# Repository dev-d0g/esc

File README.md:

4 layer STM32-based trapezoidal ESC with high/low-side PWM control

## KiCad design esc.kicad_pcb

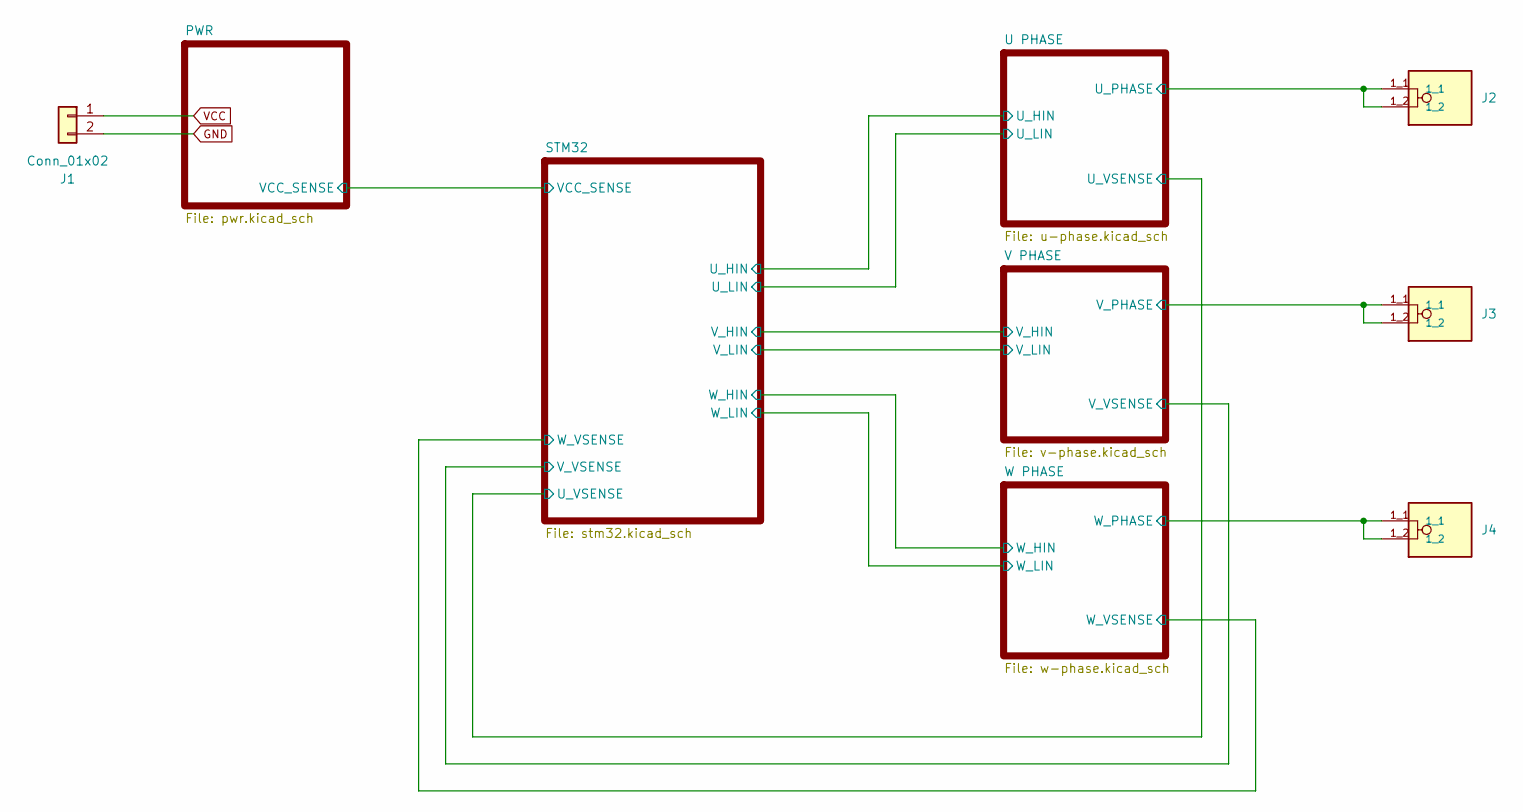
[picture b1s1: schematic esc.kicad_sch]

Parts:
J1: Conn_01x02; JWT_A3963_1x02_P3.96mm_Vertical
J2, J3, J4: Screw_Terminal_01x01; PHOENIX_1706701; PARTREV 24.09.2015

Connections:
/U PHASE/U_PHASE: J2.1_1, J2.1_2; also elsewhere on the board
/V PHASE/V_PHASE: J3.1_1, J3.1_2; also elsewhere on the board
/W PHASE/W_PHASE: J4.1_1, J4.1_2; also elsewhere on the board
GND: J1.2; also elsewhere on the board
VCC: J1.1; also elsewhere on the board

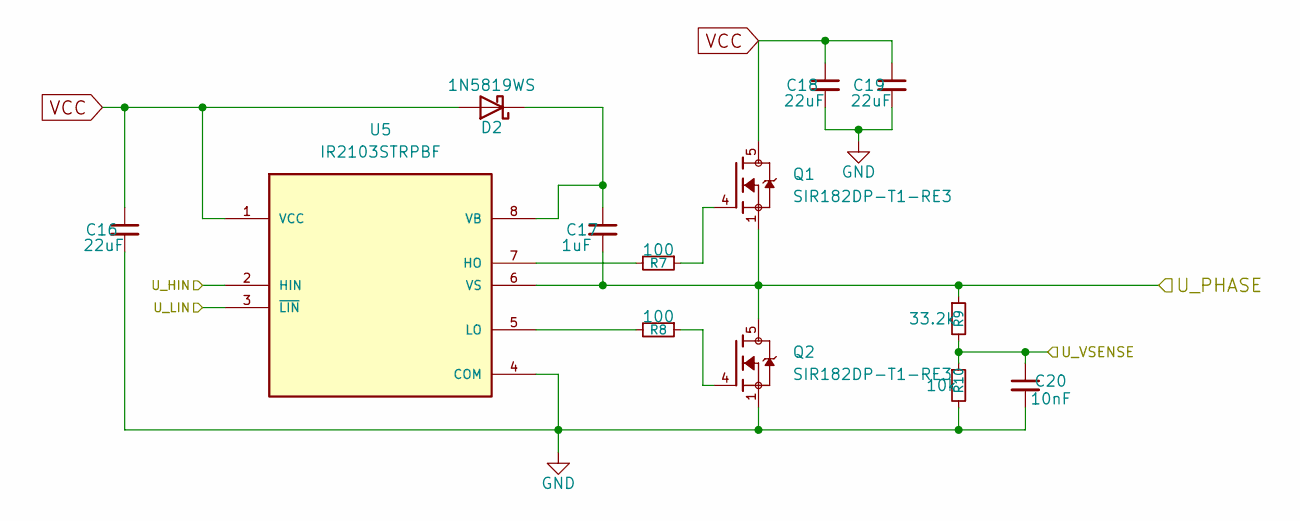
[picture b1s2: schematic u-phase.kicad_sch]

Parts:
C16, C18, C19: 22uF; C_1206_3216Metric
C17: 1uF; C_0805_2012Metric
C20: 10nF; C_0603_1608Metric
D2: 1N5819WS; D_SOD-323
Q1, Q2: SIR182DP-T1-RE3; TRANS_SIR182DP-T1-RE3; PARTREV B
R7, R8: 100; R_1206_3216Metric
R9: 33.2k; R_0805_2012Metric
R10: 10k; R_0805_2012Metric
U5: IR2103STRPBF; SOIC127P600X175-8N; PARTREV April 18, 2013

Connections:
/STM32/U_HIN: U5.2 (HIN); also elsewhere on the board
/STM32/U_LIN: U5.3 (~LIN); also elsewhere on the board
/STM32/U_VSENSE: C20.1, R9.2, R10.1; also elsewhere on the board
/U PHASE/U_PHASE: C17.2, Q1.1, Q1.2, Q1.3, Q2.5, Q2.6, Q2.7, Q2.8, Q2.9, R9.1, U5.6 (VS); also elsewhere on the board
GND: C16.2, C18.2, C19.2, C20.2, Q2.1, Q2.2, Q2.3, R10.2, U5.4 (COM); also elsewhere on the board
unnamed: C17.1, D2.1 (K), U5.8 (VB)
unnamed: Q1.4, R7.1
unnamed: Q2.4, R8.1
unnamed: R7.2, U5.7 (HO)
unnamed: R8.2, U5.5 (LO)
VCC: C16.1, C18.1, C19.1, D2.2 (A), Q1.5, Q1.6, Q1.7, Q1.8, Q1.9, U5.1 (VCC); also elsewhere on the board

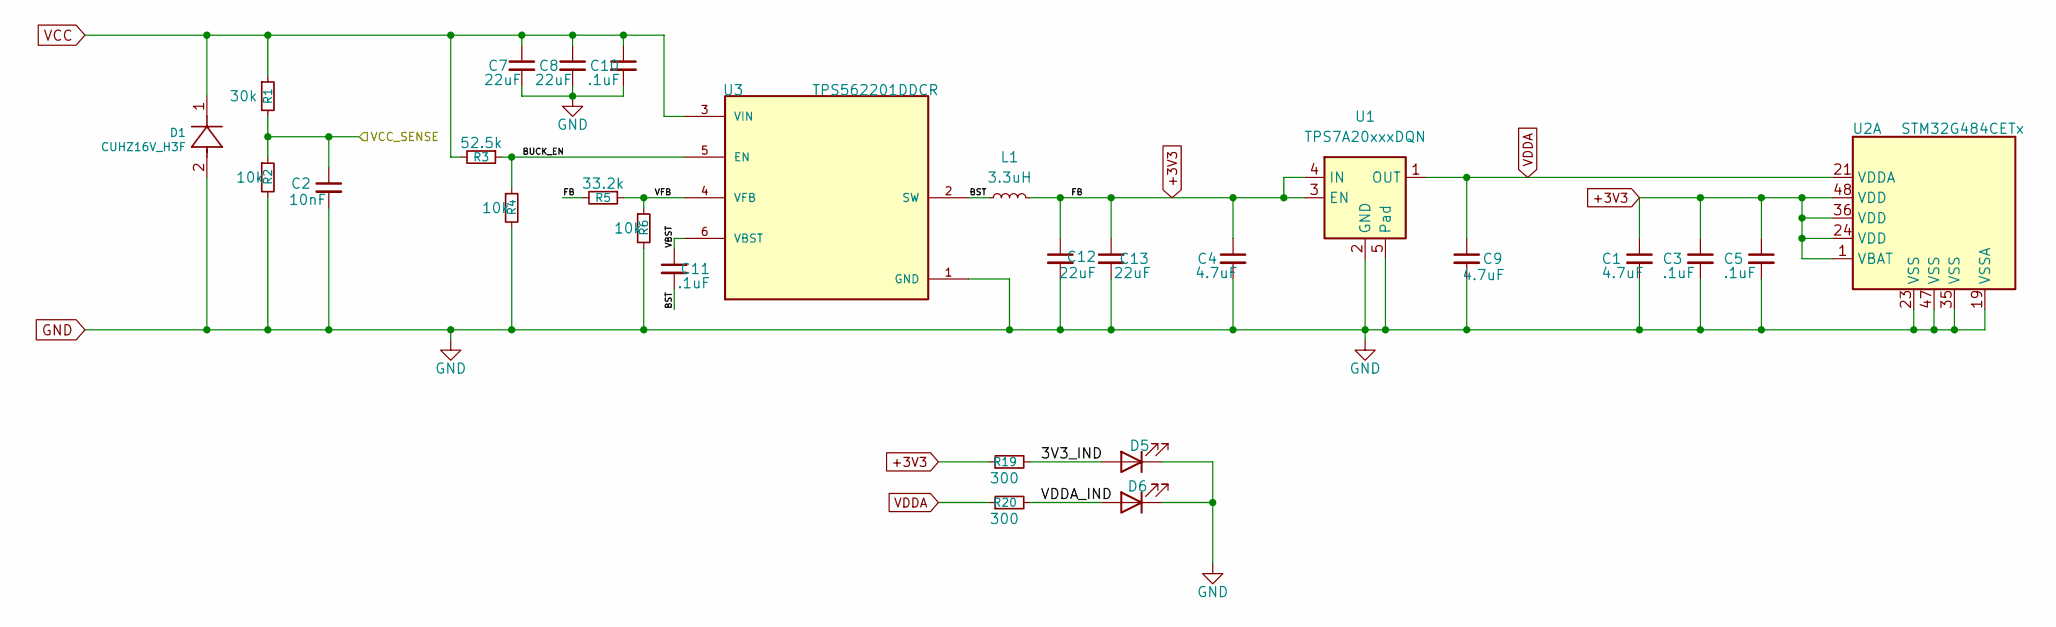
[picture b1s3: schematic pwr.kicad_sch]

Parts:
C1, C4, C9: 4.7uF; C_0805_2012Metric
C2: 10nF; C_0603_1608Metric
C3, C5, C10, C11: .1uF; C_0805_2012Metric
C7, C8, C12, C13: 22uF; C_1206_3216Metric
D1: CUHZ16V_H3F; SOD-323HEUS2H_TOS
D5, D6: LED; LED_0805_2012Metric
L1: 3.3uH; INDC2012X145N
R1: 30k; R_0805_2012Metric
R2, R4, R6: 10k; R_0805_2012Metric
R3: 52.5k; R_0805_2012Metric
R5: 33.2k; R_0805_2012Metric
R19, R20: 300; R_0805_2012Metric
U1: TPS7A20xxxDQN; Texas_X2SON-4_1x1mm_P0.65mm
U2: STM32G484CETx; LQFP-48_7x7mm_P0.5mm
U3: TPS562201DDCR; SOT95P280X110-6N; PARTREV A

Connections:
+3V3: C1.1, C3.1, C4.1, C5.1, C12.1, C13.1, L1.2, R5.2, R19.1, U1.3 (EN), U1.4 (IN), U2.1 (VBAT), U2.24 (VDD), U2.36 (VDD), U2.48 (VDD); also elsewhere on the board
/PWR/3V3_IND: D5.2 (A), R19.2
/PWR/BST: C11.2, L1.1, U3.2 (SW)
/PWR/BUCK_EN: R3.1, R4.1, U3.5 (EN)
/PWR/VBST: C11.1, U3.6 (VBST)
/PWR/VCC_SENSE: C2.1, R1.2, R2.1; also elsewhere on the board
/PWR/VDDA_IND: D6.2 (A), R20.2
/PWR/VFB: R5.1, R6.1, U3.4 (VFB)
GND: C1.2, C2.2, C3.2, C4.2, C5.2, C7.2, C8.2, C9.2, C10.2, C12.2, C13.2, D1.2, D5.1 (K), D6.1 (K), R2.2, R4.2, R6.2, U1.2 (GND), U1.5 (Pad), U2.19 (VSSA), U2.23 (VSS), U2.35 (VSS), U2.47 (VSS), U3.1 (GND); also elsewhere on the board
VCC: C7.1, C8.1, C10.1, D1.1, R1.1, R3.2, U3.3 (VIN); also elsewhere on the board
VDDA: C9.1, R20.1, U1.1 (OUT), U2.21 (VDDA); also elsewhere on the board

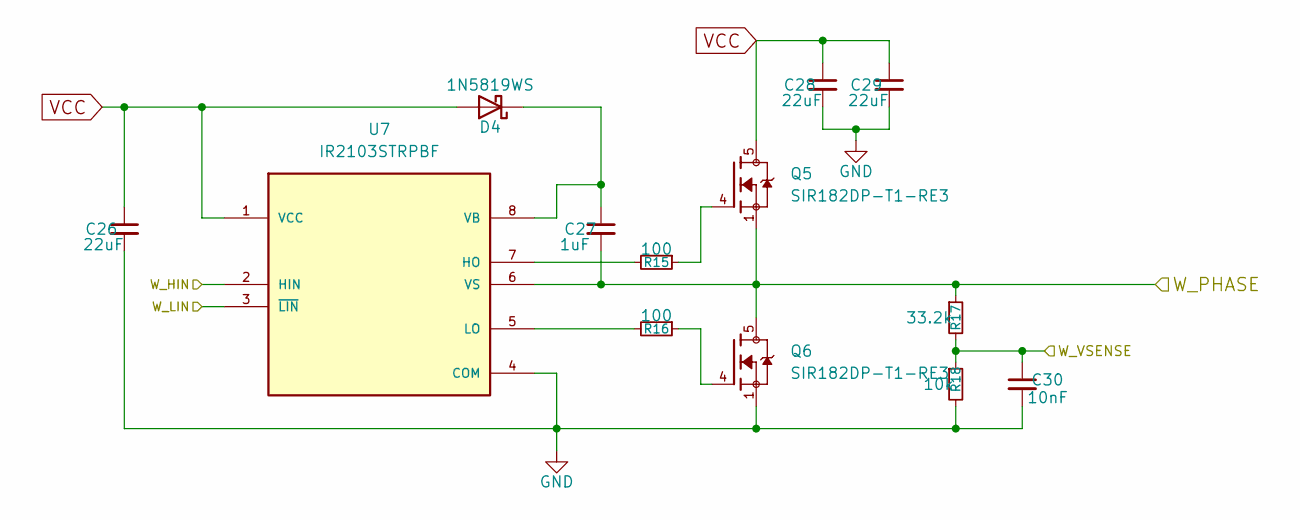
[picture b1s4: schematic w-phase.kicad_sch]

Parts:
C26, C28, C29: 22uF; C_1206_3216Metric
C27: 1uF; C_0805_2012Metric
C30: 10nF; C_0603_1608Metric
D4: 1N5819WS; D_SOD-323
Q5, Q6: SIR182DP-T1-RE3; TRANS_SIR182DP-T1-RE3; PARTREV B
R15, R16: 100; R_1206_3216Metric
R17: 33.2k; R_0805_2012Metric
R18: 10k; R_0805_2012Metric
U7: IR2103STRPBF; SOIC127P600X175-8N; PARTREV April 18, 2013

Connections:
/STM32/W_HIN: U7.2 (HIN); also elsewhere on the board
/STM32/W_LIN: U7.3 (~LIN); also elsewhere on the board
/STM32/W_VSENSE: C30.1, R17.2, R18.1; also elsewhere on the board
/W PHASE/W_PHASE: C27.2, Q5.1, Q5.2, Q5.3, Q6.5, Q6.6, Q6.7, Q6.8, Q6.9, R17.1, U7.6 (VS); also elsewhere on the board
GND: C26.2, C28.2, C29.2, C30.2, Q6.1, Q6.2, Q6.3, R18.2, U7.4 (COM); also elsewhere on the board
unnamed: C27.1, D4.1 (K), U7.8 (VB)
unnamed: Q5.4, R15.1
unnamed: Q6.4, R16.1
unnamed: R15.2, U7.7 (HO)
unnamed: R16.2, U7.5 (LO)
VCC: C26.1, C28.1, C29.1, D4.2 (A), Q5.5, Q5.6, Q5.7, Q5.8, Q5.9, U7.1 (VCC); also elsewhere on the board

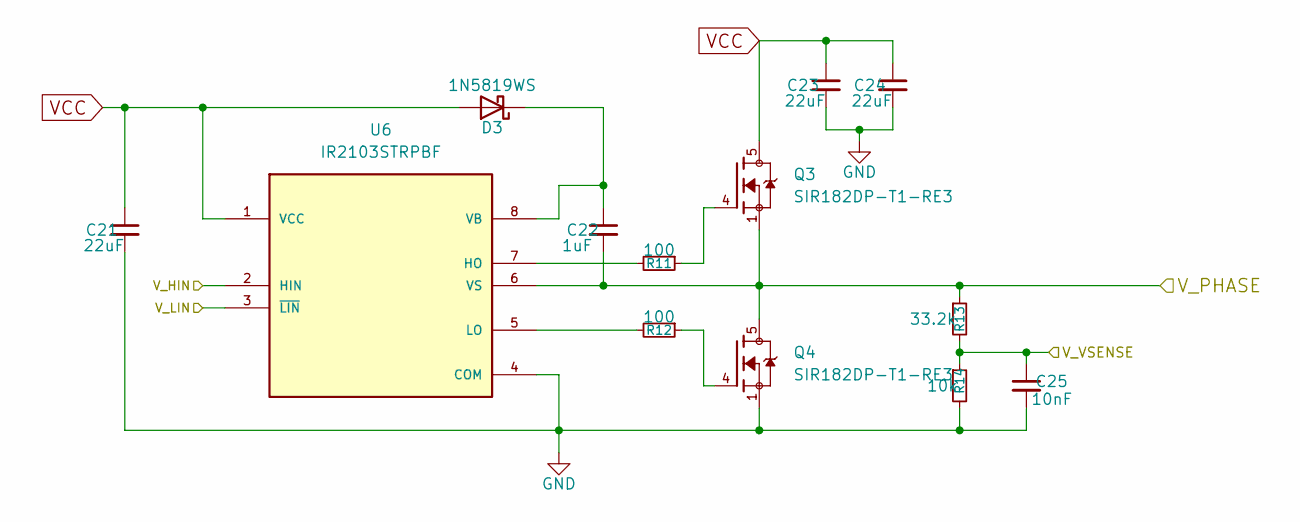
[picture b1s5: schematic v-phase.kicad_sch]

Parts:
C21, C23, C24: 22uF; C_1206_3216Metric
C22: 1uF; C_0805_2012Metric
C25: 10nF; C_0603_1608Metric
D3: 1N5819WS; D_SOD-323
Q3, Q4: SIR182DP-T1-RE3; TRANS_SIR182DP-T1-RE3; PARTREV B
R11, R12: 100; R_1206_3216Metric
R13: 33.2k; R_0805_2012Metric
R14: 10k; R_0805_2012Metric
U6: IR2103STRPBF; SOIC127P600X175-8N; PARTREV April 18, 2013

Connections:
/STM32/V_HIN: U6.2 (HIN); also elsewhere on the board
/STM32/V_LIN: U6.3 (~LIN); also elsewhere on the board
/STM32/V_VSENSE: C25.1, R13.2, R14.1; also elsewhere on the board
/V PHASE/V_PHASE: C22.2, Q3.1, Q3.2, Q3.3, Q4.5, Q4.6, Q4.7, Q4.8, Q4.9, R13.1, U6.6 (VS); also elsewhere on the board
GND: C21.2, C23.2, C24.2, C25.2, Q4.1, Q4.2, Q4.3, R14.2, U6.4 (COM); also elsewhere on the board
unnamed: C22.1, D3.1 (K), U6.8 (VB)
unnamed: Q3.4, R11.1
unnamed: Q4.4, R12.1
unnamed: R11.2, U6.7 (HO)
unnamed: R12.2, U6.5 (LO)
VCC: C21.1, C23.1, C24.1, D3.2 (A), Q3.5, Q3.6, Q3.7, Q3.8, Q3.9, U6.1 (VCC); also elsewhere on the board

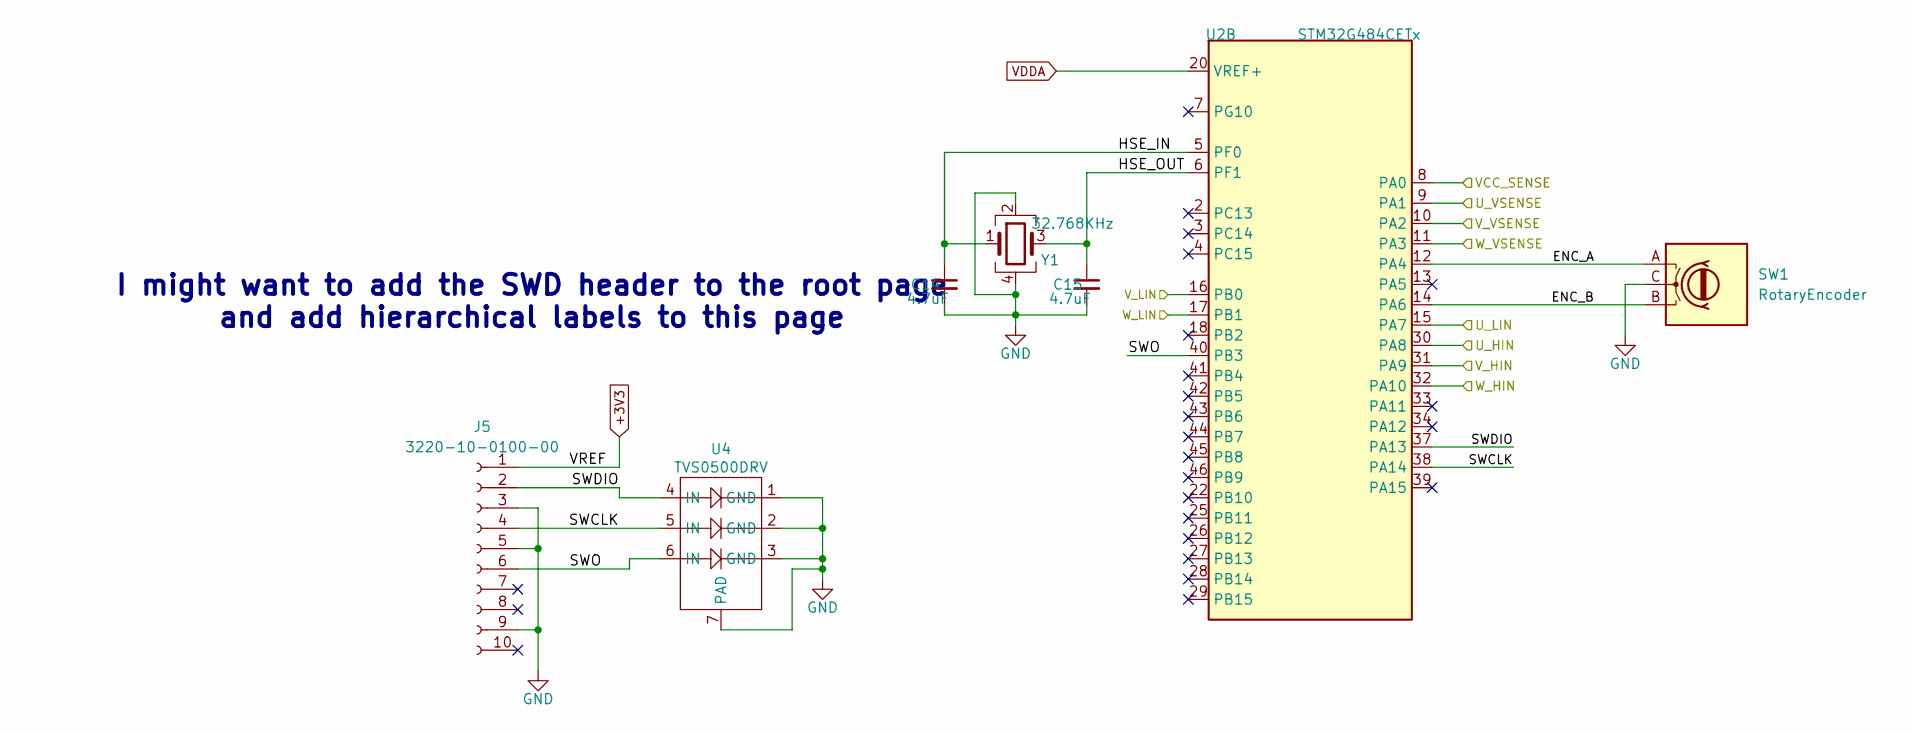
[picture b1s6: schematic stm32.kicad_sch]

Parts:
C14, C15: 4.7uF; C_0805_2012Metric
J5: 3220-10-0100-00; CONN_3220-10-0100-00_CNC
SW1: RotaryEncoder; RotaryEncoder_Alps_EC11E-Switch_Vertical_H20mm
U2: STM32G484CETx; LQFP-48_7x7mm_P0.5mm
U4: TVS0500DRV; SON65P200X200X80-7N
Y1: 32.768KHz; XTAL_ABS04W-32.768KHZ-4-D2-T5; PARTREV 12.18.2018

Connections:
+3V3: J5.1; also elsewhere on the board
/PWR/VCC_SENSE: U2.8 (PA0); also elsewhere on the board
/STM32/ENC_A: SW1.A, U2.12 (PA4)
/STM32/ENC_B: SW1.B, U2.14 (PA6)
/STM32/HSE_IN: C14.1, U2.5 (PF0), Y1.1
/STM32/HSE_OUT: C15.1, U2.6 (PF1), Y1.3
/STM32/SWCLK: J5.4, U2.38 (PA14), U4.5 (IN)
/STM32/SWDIO: J5.2, U2.37 (PA13), U4.4 (IN)
/STM32/SWO: J5.6, U2.40 (PB3), U4.6 (IN)
/STM32/U_HIN: U2.30 (PA8); also elsewhere on the board
/STM32/U_LIN: U2.15 (PA7); also elsewhere on the board
/STM32/U_VSENSE: U2.9 (PA1); also elsewhere on the board
/STM32/V_HIN: U2.31 (PA9); also elsewhere on the board
/STM32/V_LIN: U2.16 (PB0); also elsewhere on the board
/STM32/V_VSENSE: U2.10 (PA2); also elsewhere on the board
/STM32/W_HIN: U2.32 (PA10); also elsewhere on the board
/STM32/W_LIN: U2.17 (PB1); also elsewhere on the board
/STM32/W_VSENSE: U2.11 (PA3); also elsewhere on the board
GND: C14.2, C15.2, J5.3, J5.5, J5.9, SW1.C, U4.1 (GND), U4.2 (GND), U4.3 (GND), U4.7 (PAD), Y1.2, Y1.4; also elsewhere on the board
VDDA: U2.20 (VREF+); also elsewhere on the board

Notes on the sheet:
I might want to add the SWD header to the root page and add hierarchical labels to this page

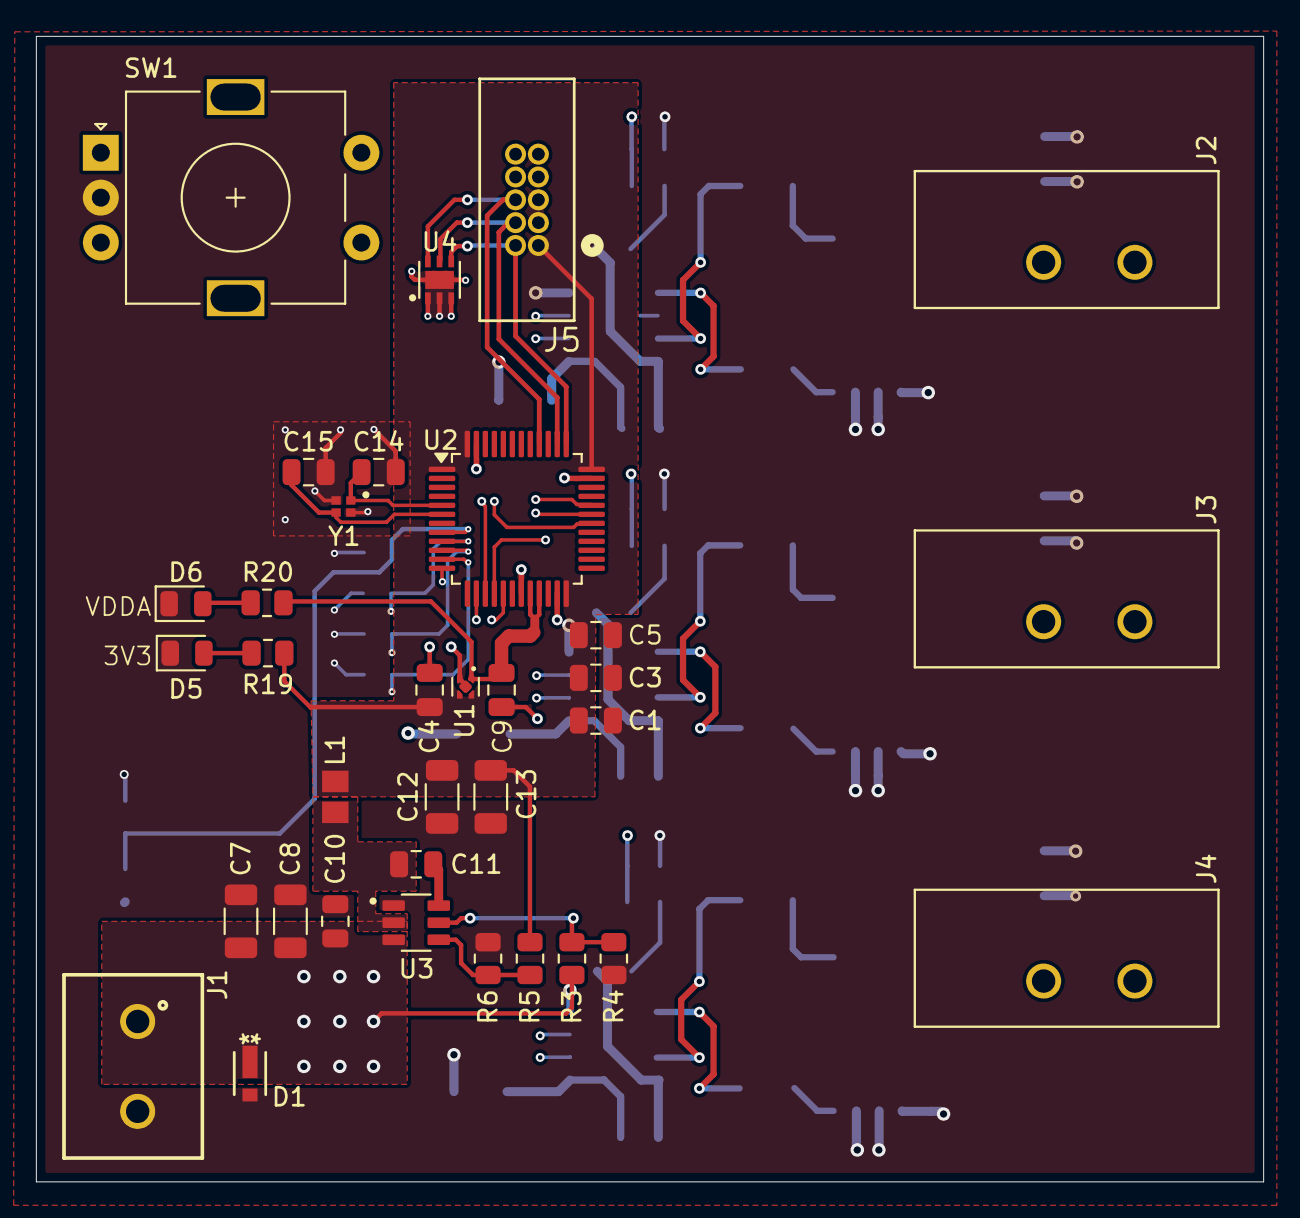
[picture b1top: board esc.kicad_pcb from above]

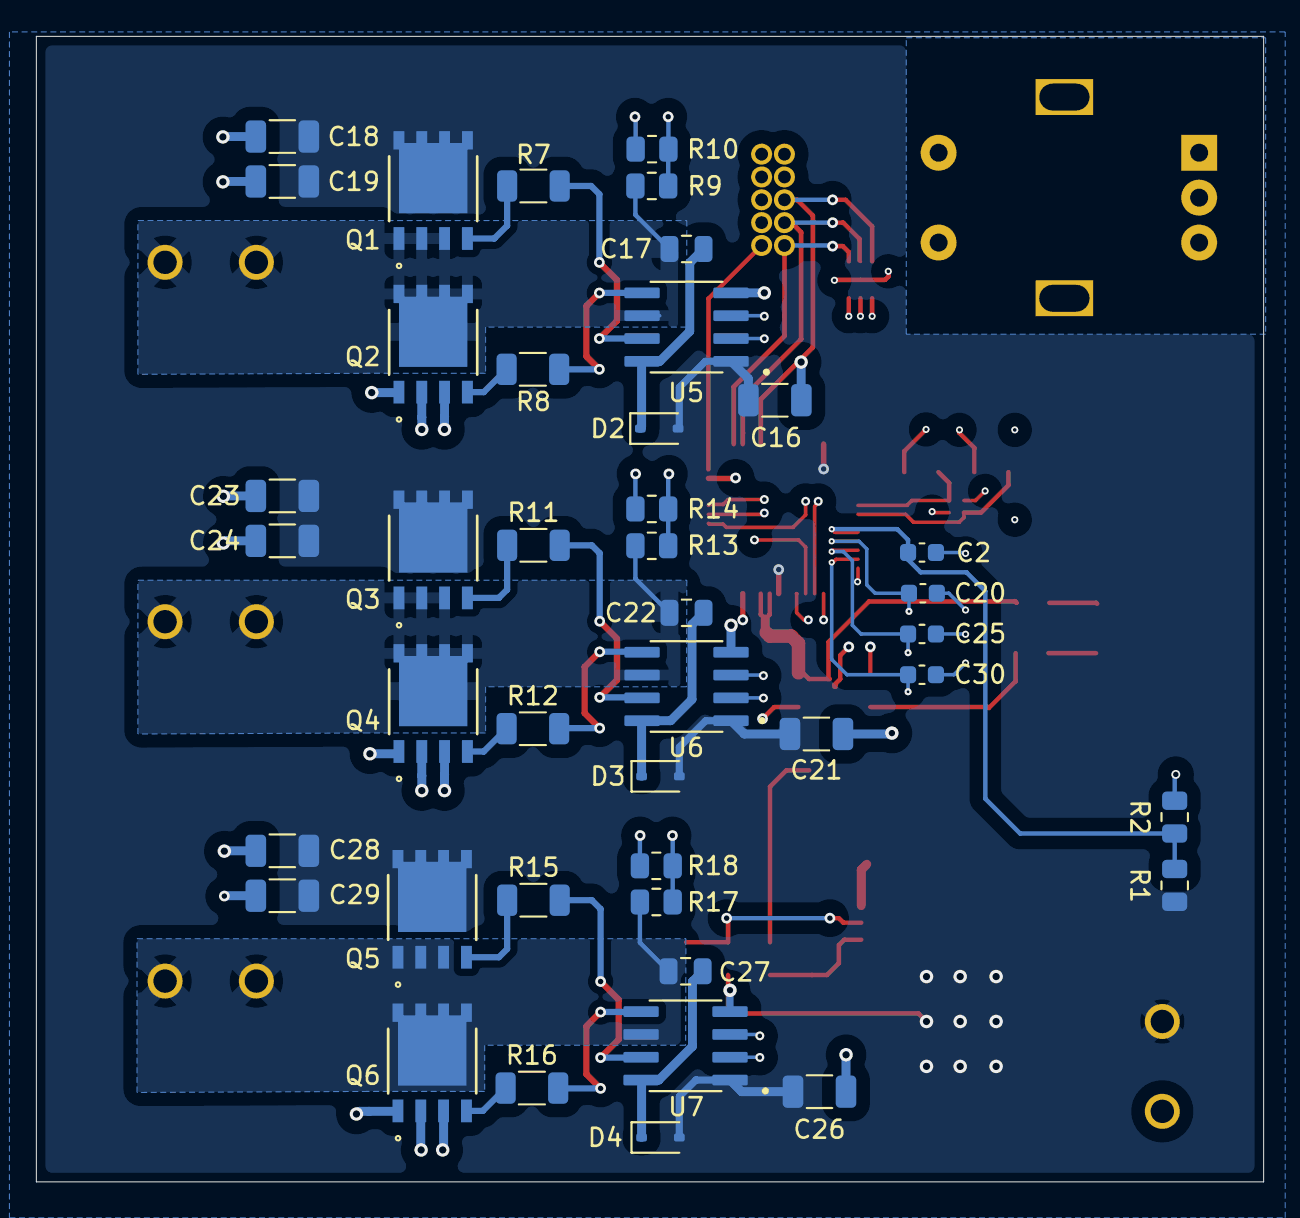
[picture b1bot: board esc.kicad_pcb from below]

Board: 4 copper layers, 68.3 x 63.8 mm, 76 parts (42 on the bottom side), 45 nets.

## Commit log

2025-09-07 Initial commit -- existing KiCad project
2025-09-07 Removing ignored files from repo
2025-09-07 Buck layout; MOSFET layout
2025-09-07 Added Digikey Downloads
2025-09-10 MOSFET placement
2025-09-10 Crystal routing/placement
2025-09-11 3V3 and VDDA placement
2025-09-13 PDN complete
2025-09-14 completed layout -- DRC
2025-09-18 cleaning up routing
2025-09-24 routing cleanup
2025-09-25 cleaning routing
2025-10-03 cleaning sensing routing
2025-10-19 SWD TVS routing
2025-10-19 DRC cleanup
2025-10-23 silkscreen cleanup
2025-12-21 improving MOSFET decap placements
2025-12-22 adding description
2025-12-22 fab outputs
